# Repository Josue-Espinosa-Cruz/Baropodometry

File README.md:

# Baropodometry

1. **Printed Circuit Board:** 3D renders
    ~~~
    Electronic CAD: Autodesk EAGLE
    Computer-Aided Design Software: Fusion360

	1. Schematic Diagram
	2. CAD Model
	3. Renders
    ~~~
2. **Microcontroller:** Programming embedded system to acquire and visualize static plantar load distribution.
    ~~~
    Embedded System: MSP430-F5529 Launchpad
    Manufacturer:Texas Instruments 
    General specifications: 25 MHz MCU with 128KB Flash, 8KB SRAM
    ~~~

**Features applied:**
  1. GPIO pins
  2. Timer_A0
  3. 12-bit ADC
  4. UART protocol
  5. Interrupts

## Credits
I would like to express special thanks to the following users on GrabCAD for their CAD models:

  1. Female Headers By DL2DW - Dirk Wouters
  2. Jumpler By DL2DW - Dirk Wouters
  3. Male Headers By - Vahagn Zargaryan
  4. Mini USB By [Unknown]

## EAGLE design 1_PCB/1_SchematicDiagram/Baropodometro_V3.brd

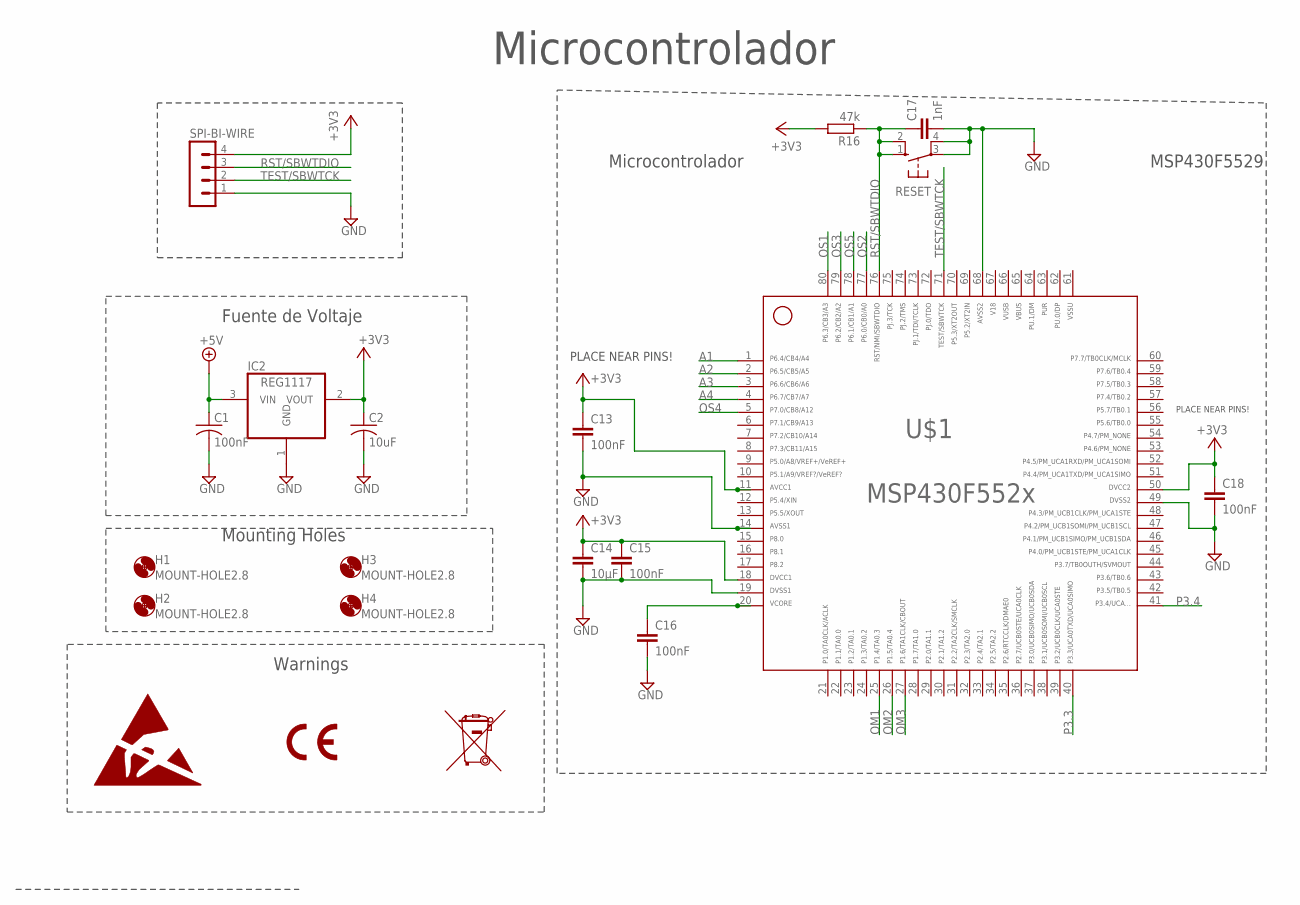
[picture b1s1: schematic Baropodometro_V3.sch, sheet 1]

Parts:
C1, C13, C15, C16, C18: 100nF; C0805
C2: 10uF; C0805
C14: 10µF; C0805
C17: 1nF; C0805
H1, H2, H3, H4: MOUNT-HOLE2.8; 2,8
IC2: REG1117; SOT223
R16: 47k; R0805
RESET: 10-XX; B3F-10XX
SPI-BI-WIRE: MA04-1
U$1: MSP430F5529; TI_MSP430_V16_INTERN_PN80

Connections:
61: U$1.61
65: U$1.65
66: U$1.66
67: U$1.67
+3V3: C2.1, C13.1, C14.1, C15.1, C18.1, IC2.2 (VOUT), R16.2, SPI-BI-WIRE.4, U$1.11, U$1.18, U$1.50; also elsewhere on the board
+5V: C1.1, IC2.3 (VIN); also elsewhere on the board
A1: U$1.1; also elsewhere on the board
A2: U$1.2; also elsewhere on the board
A3: U$1.3; also elsewhere on the board
A4: U$1.4; also elsewhere on the board
GND: C1.2, C2.2, C13.2, C14.2, C15.2, C16.2, C17.2, C18.2, IC2.1 (GND), RESET.3, RESET.4 (P1), SPI-BI-WIRE.1, U$1.14, U$1.19, U$1.49, U$1.68; also elsewhere on the board
unnamed: C16.1, U$1.20
OM1: U$1.25; also elsewhere on the board
OM2: U$1.26; also elsewhere on the board
OM3: U$1.27; also elsewhere on the board
OS1: U$1.80; also elsewhere on the board
OS2: U$1.77; also elsewhere on the board
OS3: U$1.79; also elsewhere on the board
OS4: U$1.5; also elsewhere on the board
OS5: U$1.78; also elsewhere on the board
P3.3: U$1.40; also elsewhere on the board
P3.4: U$1.41; also elsewhere on the board
RST/SBWTDIO: C17.1, R16.1, RESET.1 (S), RESET.2 (S1), SPI-BI-WIRE.3, U$1.76
TEST/SBWTCK: SPI-BI-WIRE.2, U$1.71

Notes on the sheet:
Fuente de Voltaje
Microcontrolador
MSP430F5529
Warnings
Mounting Holes
PLACE NEAR PINS!

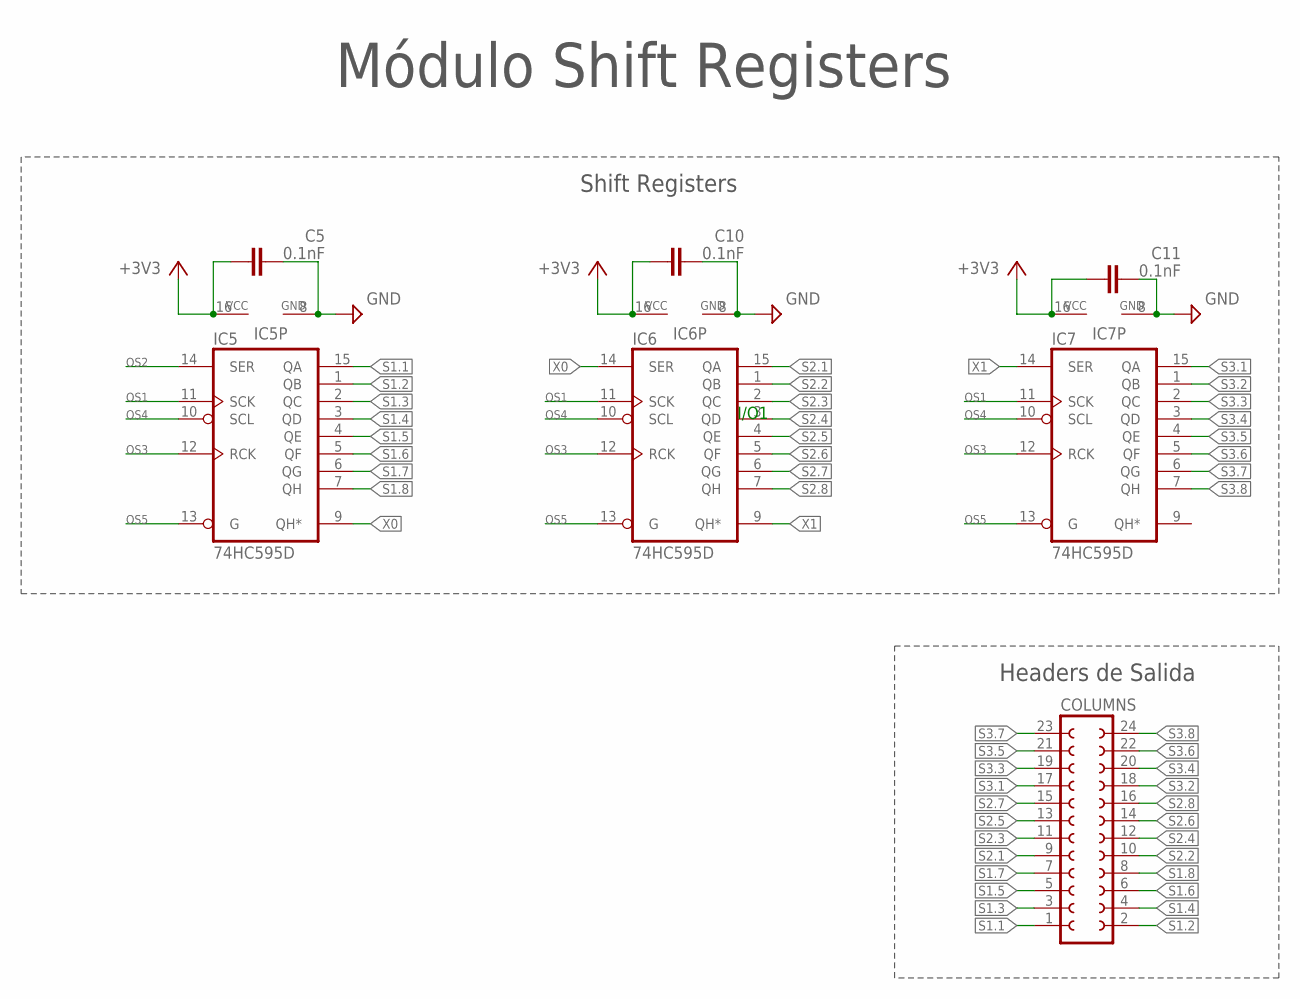
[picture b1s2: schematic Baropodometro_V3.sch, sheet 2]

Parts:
C5, C10, C11: 0.1nF; C0805
COLUMNS: FE12-2W
IC5, IC6, IC7: 74HC595D; SO16

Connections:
+3V3: C5.1, C10.1, C11.1, IC5.16 (VCC), IC6.16 (VCC), IC7.16 (VCC); also elsewhere on the board
GND: C5.2, C10.2, C11.2, IC5.8 (GND), IC6.8 (GND), IC7.8 (GND); also elsewhere on the board
OS1: IC5.11 (SCK), IC6.11 (SCK), IC7.11 (SCK); also elsewhere on the board
OS2: IC5.14 (SER); also elsewhere on the board
OS3: IC5.12 (RCK), IC6.12 (RCK), IC7.12 (RCK); also elsewhere on the board
OS4: IC5.10 (SCL), IC6.10 (SCL), IC7.10 (SCL); also elsewhere on the board
OS5: IC5.13 (G), IC6.13 (G), IC7.13 (G); also elsewhere on the board
S1.1: COLUMNS.1, IC5.15 (QA)
S1.2: COLUMNS.2, IC5.1 (QB)
S1.3: COLUMNS.3, IC5.2 (QC)
S1.4: COLUMNS.4, IC5.3 (QD)
S1.5: COLUMNS.5, IC5.4 (QE)
S1.6: COLUMNS.6, IC5.5 (QF)
S1.7: COLUMNS.7, IC5.6 (QG)
S1.8: COLUMNS.8, IC5.7 (QH)
S2.1: COLUMNS.9, IC6.15 (QA)
S2.2: COLUMNS.10, IC6.1 (QB)
S2.3: COLUMNS.11, IC6.2 (QC)
S2.4: COLUMNS.12, IC6.3 (QD)
S2.5: COLUMNS.13, IC6.4 (QE)
S2.6: COLUMNS.14, IC6.5 (QF)
S2.7: COLUMNS.15, IC6.6 (QG)
S2.8: COLUMNS.16, IC6.7 (QH)
S3.1: COLUMNS.17, IC7.15 (QA)
S3.2: COLUMNS.18, IC7.1 (QB)
S3.3: COLUMNS.19, IC7.2 (QC)
S3.4: COLUMNS.20, IC7.3 (QD)
S3.5: COLUMNS.21, IC7.4 (QE)
S3.6: COLUMNS.22, IC7.5 (QF)
S3.7: COLUMNS.23, IC7.6 (QG)
S3.8: COLUMNS.24, IC7.7 (QH)
X0: IC5.9 (QH*), IC6.14 (SER)
X1: IC6.9 (QH*), IC7.14 (SER)

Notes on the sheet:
I/O1
Shift Registers
Módulo Shift Registers
Headers de Salida

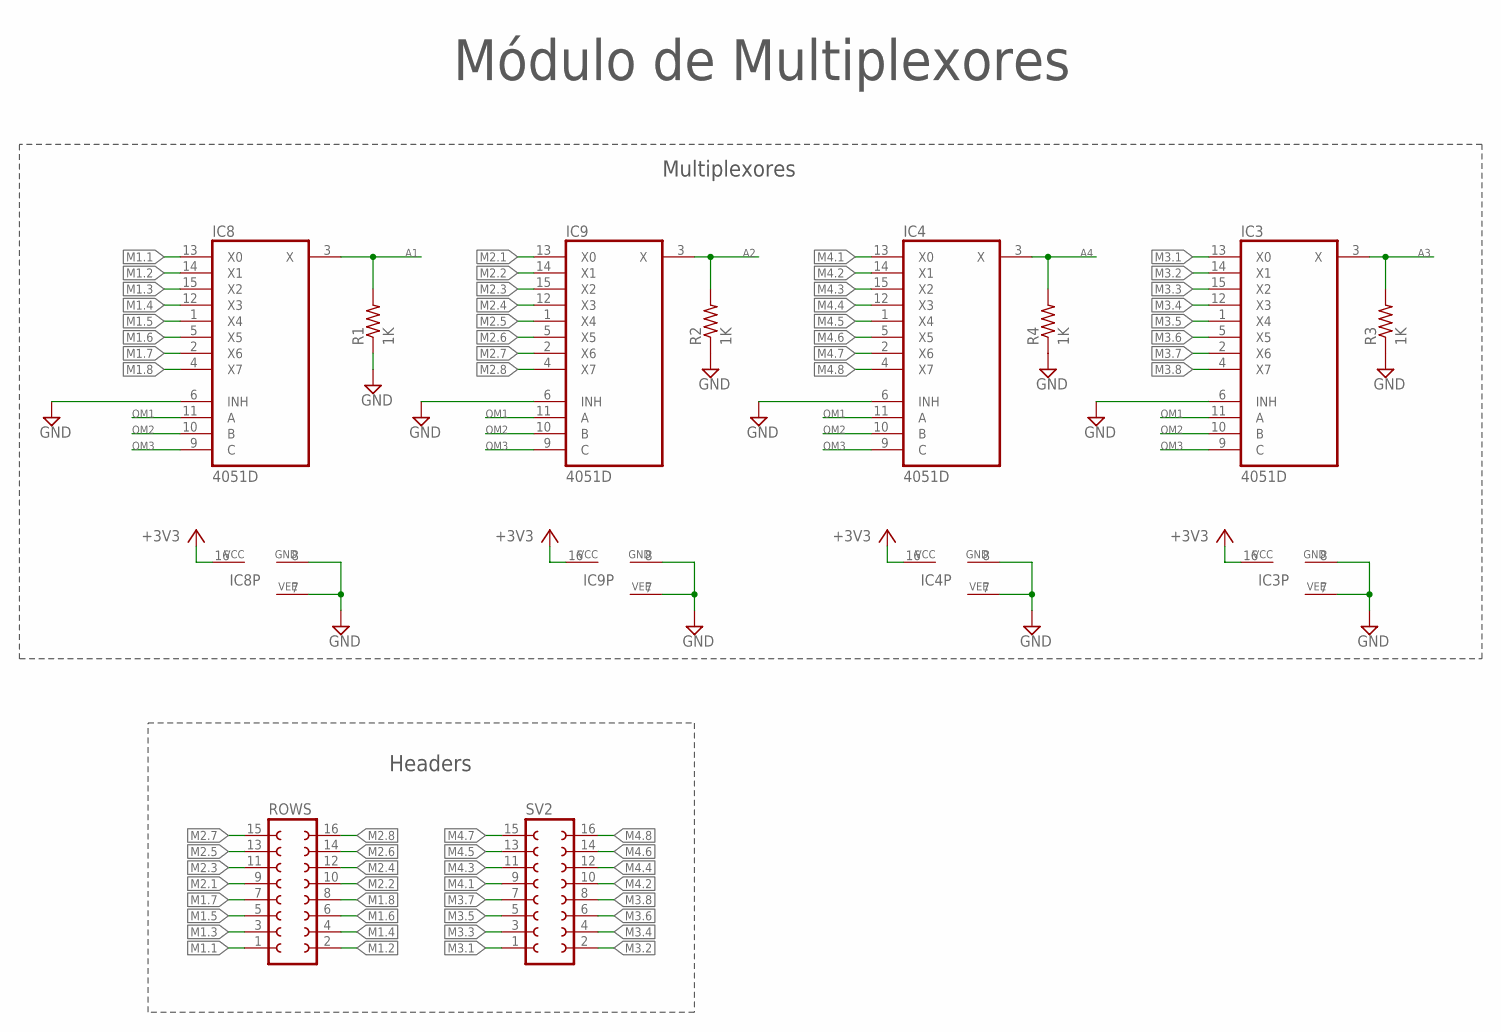
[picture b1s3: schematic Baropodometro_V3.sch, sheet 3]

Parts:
IC3, IC4, IC8, IC9: 4051D; SO16
R1, R2, R3, R4: 1K; R0805
ROWS: FE08-2W
SV2: FE08-2W

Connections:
+3V3: IC3.16 (VCC), IC4.16 (VCC), IC8.16 (VCC), IC9.16 (VCC); also elsewhere on the board
A1: IC8.3 (X), R1.2; also elsewhere on the board
A2: IC9.3 (X), R2.2; also elsewhere on the board
A3: IC3.3 (X), R3.2; also elsewhere on the board
A4: IC4.3 (X), R4.2; also elsewhere on the board
GND: IC3.6 (INH), IC3.7 (VEE), IC3.8 (GND), IC4.6 (INH), IC4.7 (VEE), IC4.8 (GND), IC8.6 (INH), IC8.7 (VEE), IC8.8 (GND), IC9.6 (INH), IC9.7 (VEE), IC9.8 (GND), R1.1, R2.1, R3.1, R4.1; also elsewhere on the board
M1.1: IC8.13 (X0), ROWS.1
M1.2: IC8.14 (X1), ROWS.2
M1.3: IC8.15 (X2), ROWS.3
M1.4: IC8.12 (X3), ROWS.4
M1.5: IC8.1 (X4), ROWS.5
M1.6: IC8.5 (X5), ROWS.6
M1.7: IC8.2 (X6), ROWS.7
M1.8: IC8.4 (X7), ROWS.8
M2.1: IC9.13 (X0), ROWS.9
M2.2: IC9.14 (X1), ROWS.10
M2.3: IC9.15 (X2), ROWS.11
M2.4: IC9.12 (X3), ROWS.12
M2.5: IC9.1 (X4), ROWS.13
M2.6: IC9.5 (X5), ROWS.14
M2.7: IC9.2 (X6), ROWS.15
M2.8: IC9.4 (X7), ROWS.16
M3.1: IC3.13 (X0), SV2.1
M3.2: IC3.14 (X1), SV2.2
M3.3: IC3.15 (X2), SV2.3
M3.4: IC3.12 (X3), SV2.4
M3.5: IC3.1 (X4), SV2.5
M3.6: IC3.5 (X5), SV2.6
M3.7: IC3.2 (X6), SV2.7
M3.8: IC3.4 (X7), SV2.8
M4.1: IC4.13 (X0), SV2.9
M4.2: IC4.14 (X1), SV2.10
M4.3: IC4.15 (X2), SV2.11
M4.4: IC4.12 (X3), SV2.12
M4.5: IC4.1 (X4), SV2.13
M4.6: IC4.5 (X5), SV2.14
M4.7: IC4.2 (X6), SV2.15
M4.8: IC4.4 (X7), SV2.16
OM1: IC3.11 (A), IC4.11 (A), IC8.11 (A), IC9.11 (A); also elsewhere on the board
OM2: IC3.10 (B), IC4.10 (B), IC8.10 (B), IC9.10 (B); also elsewhere on the board
OM3: IC3.9 (C), IC4.9 (C), IC8.9 (C), IC9.9 (C); also elsewhere on the board

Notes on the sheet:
Headers
Multiplexores
Módulo de Multiplexores

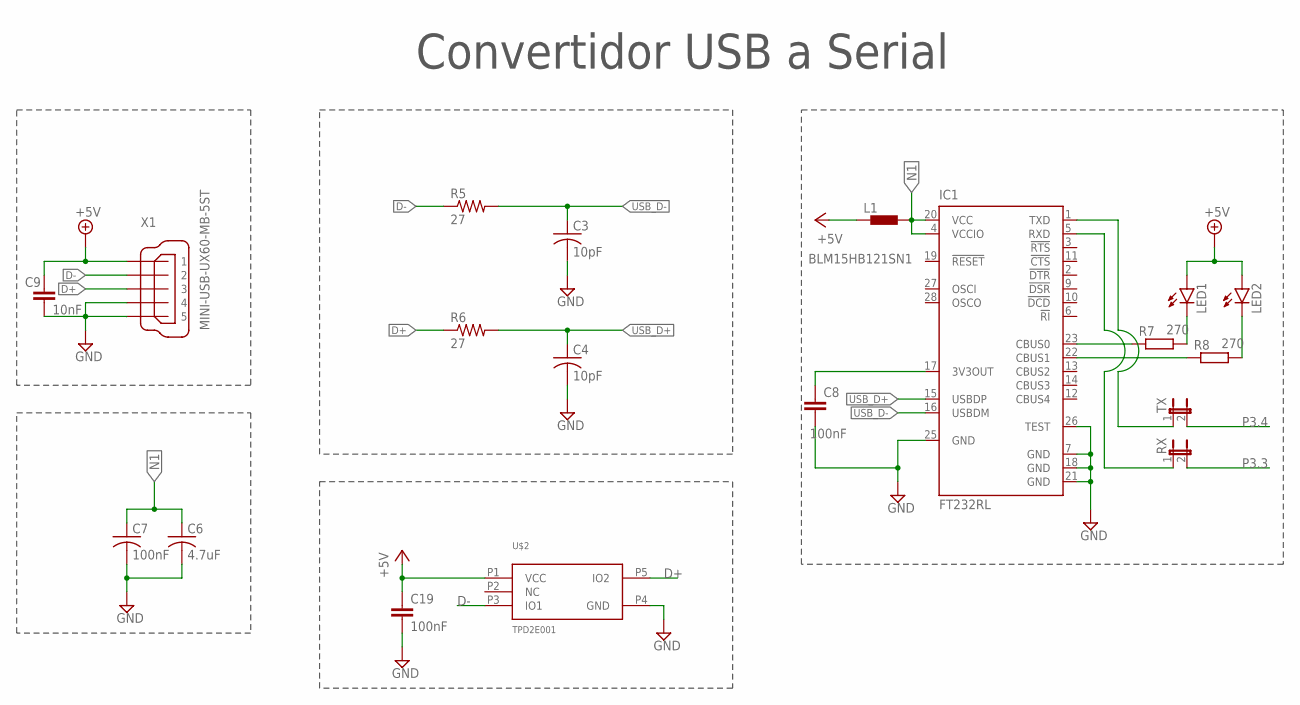
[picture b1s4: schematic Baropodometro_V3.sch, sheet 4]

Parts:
C3, C4: 10pF; C0805
C6: 4.7uF; C0805
C7, C8, C19: 100nF; C0805
C9: 10nF; C0805
IC1: FT232RL; SSOP28
L1: BLM15HB121SN1; 0402
LED1, LED2: LEDCHIP-LED0805; CHIP-LED0805
R5, R6: 27; R0805
R7, R8: 270; R0805
RX: JP1E; JP1
TX: JP1E; JP1
U$2: TPD2E001; SOT-5
X1: MINI-USB-UX60-MB-5ST; UX60-MB-5ST

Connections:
+5V: C9.1, C19.1, L1.1, LED1.A, LED2.A, U$2.P1 (VCC), X1.1; also elsewhere on the board
D+: R6.1, U$2.P5 (IO2), X1.3
D-: R5.1, U$2.P3 (IO1), X1.2
GND: C3.2, C4.2, C6.2, C7.2, C8.2, C9.2, C19.2, IC1.7 (GND), IC1.18 (GND), IC1.21 (GND), IC1.25 (GND), IC1.26 (TEST), U$2.P4 (GND), X1.4, X1.5; also elsewhere on the board
N1: C6.1, C7.1, IC1.4 (VCCIO), IC1.20 (VCC), L1.2
unnamed: LED1.C, R7.2
unnamed: IC1.22 (CBUS1), R8.1
unnamed: IC1.23 (CBUS0), R7.1
unnamed: LED2.C, R8.2
unnamed: IC1.1 (TXD), TX.1
unnamed: IC1.5 (RXD), RX.1
unnamed: C8.1, IC1.17 (3V3OUT)
P3.3: RX.2; also elsewhere on the board
P3.4: TX.2; also elsewhere on the board
USB_D+: C4.1, IC1.15 (USBDP), R6.2
USB_D-: C3.1, IC1.16 (USBDM), R5.2

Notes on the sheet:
Convertidor USB a Serial

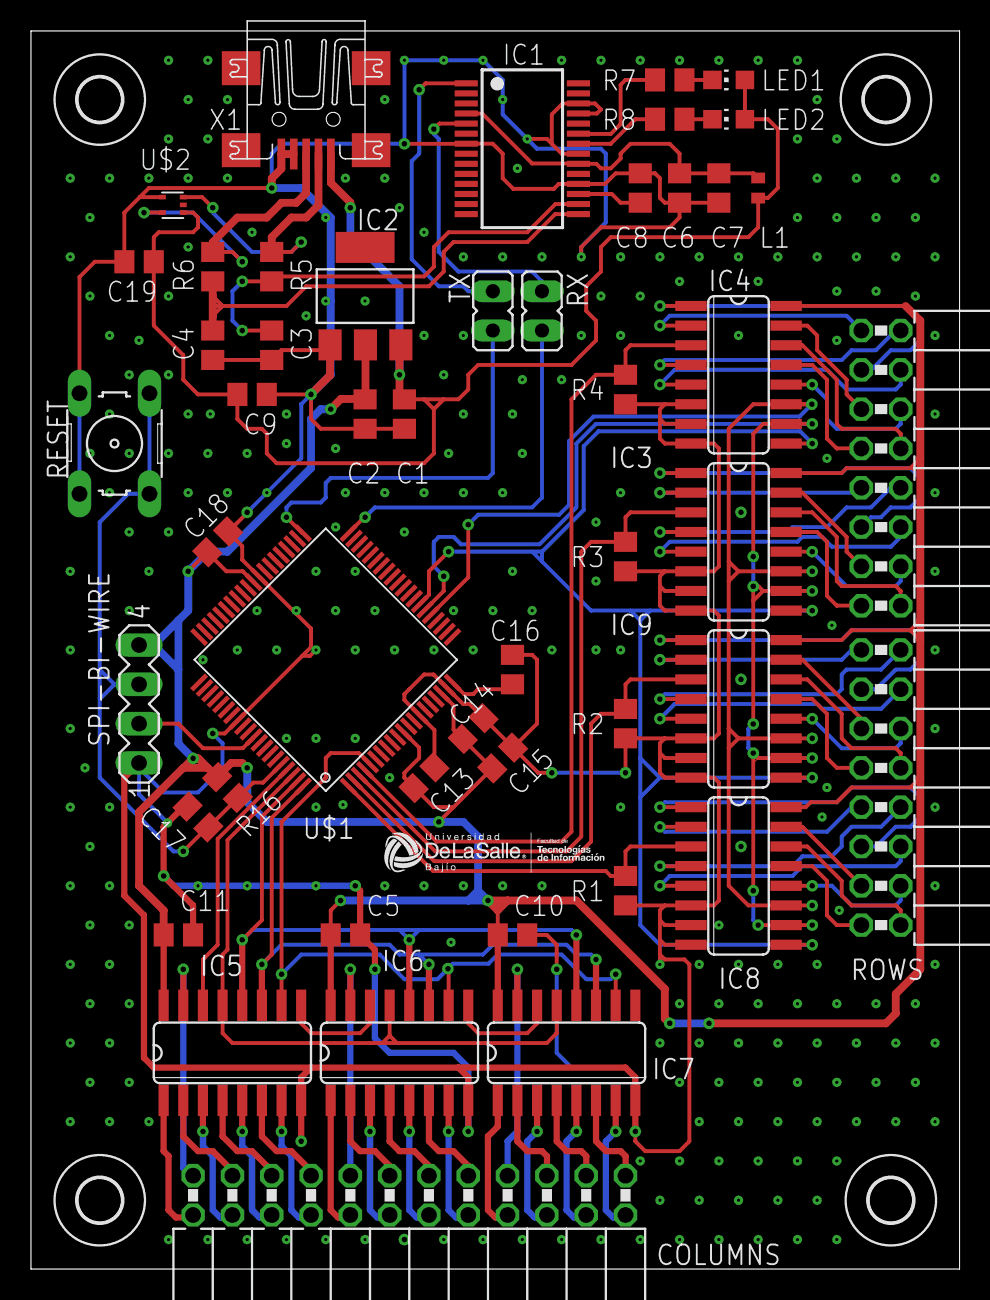
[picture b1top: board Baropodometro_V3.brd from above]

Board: 2 copper layers, 60.0 x 80.0 mm, 53 parts (0 on the bottom side), 90 nets.

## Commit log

2022-09-26 PCB and Microcontroller data
2024-05-09 Upload Diagrams folder and update README file
2024-05-09 Update files
